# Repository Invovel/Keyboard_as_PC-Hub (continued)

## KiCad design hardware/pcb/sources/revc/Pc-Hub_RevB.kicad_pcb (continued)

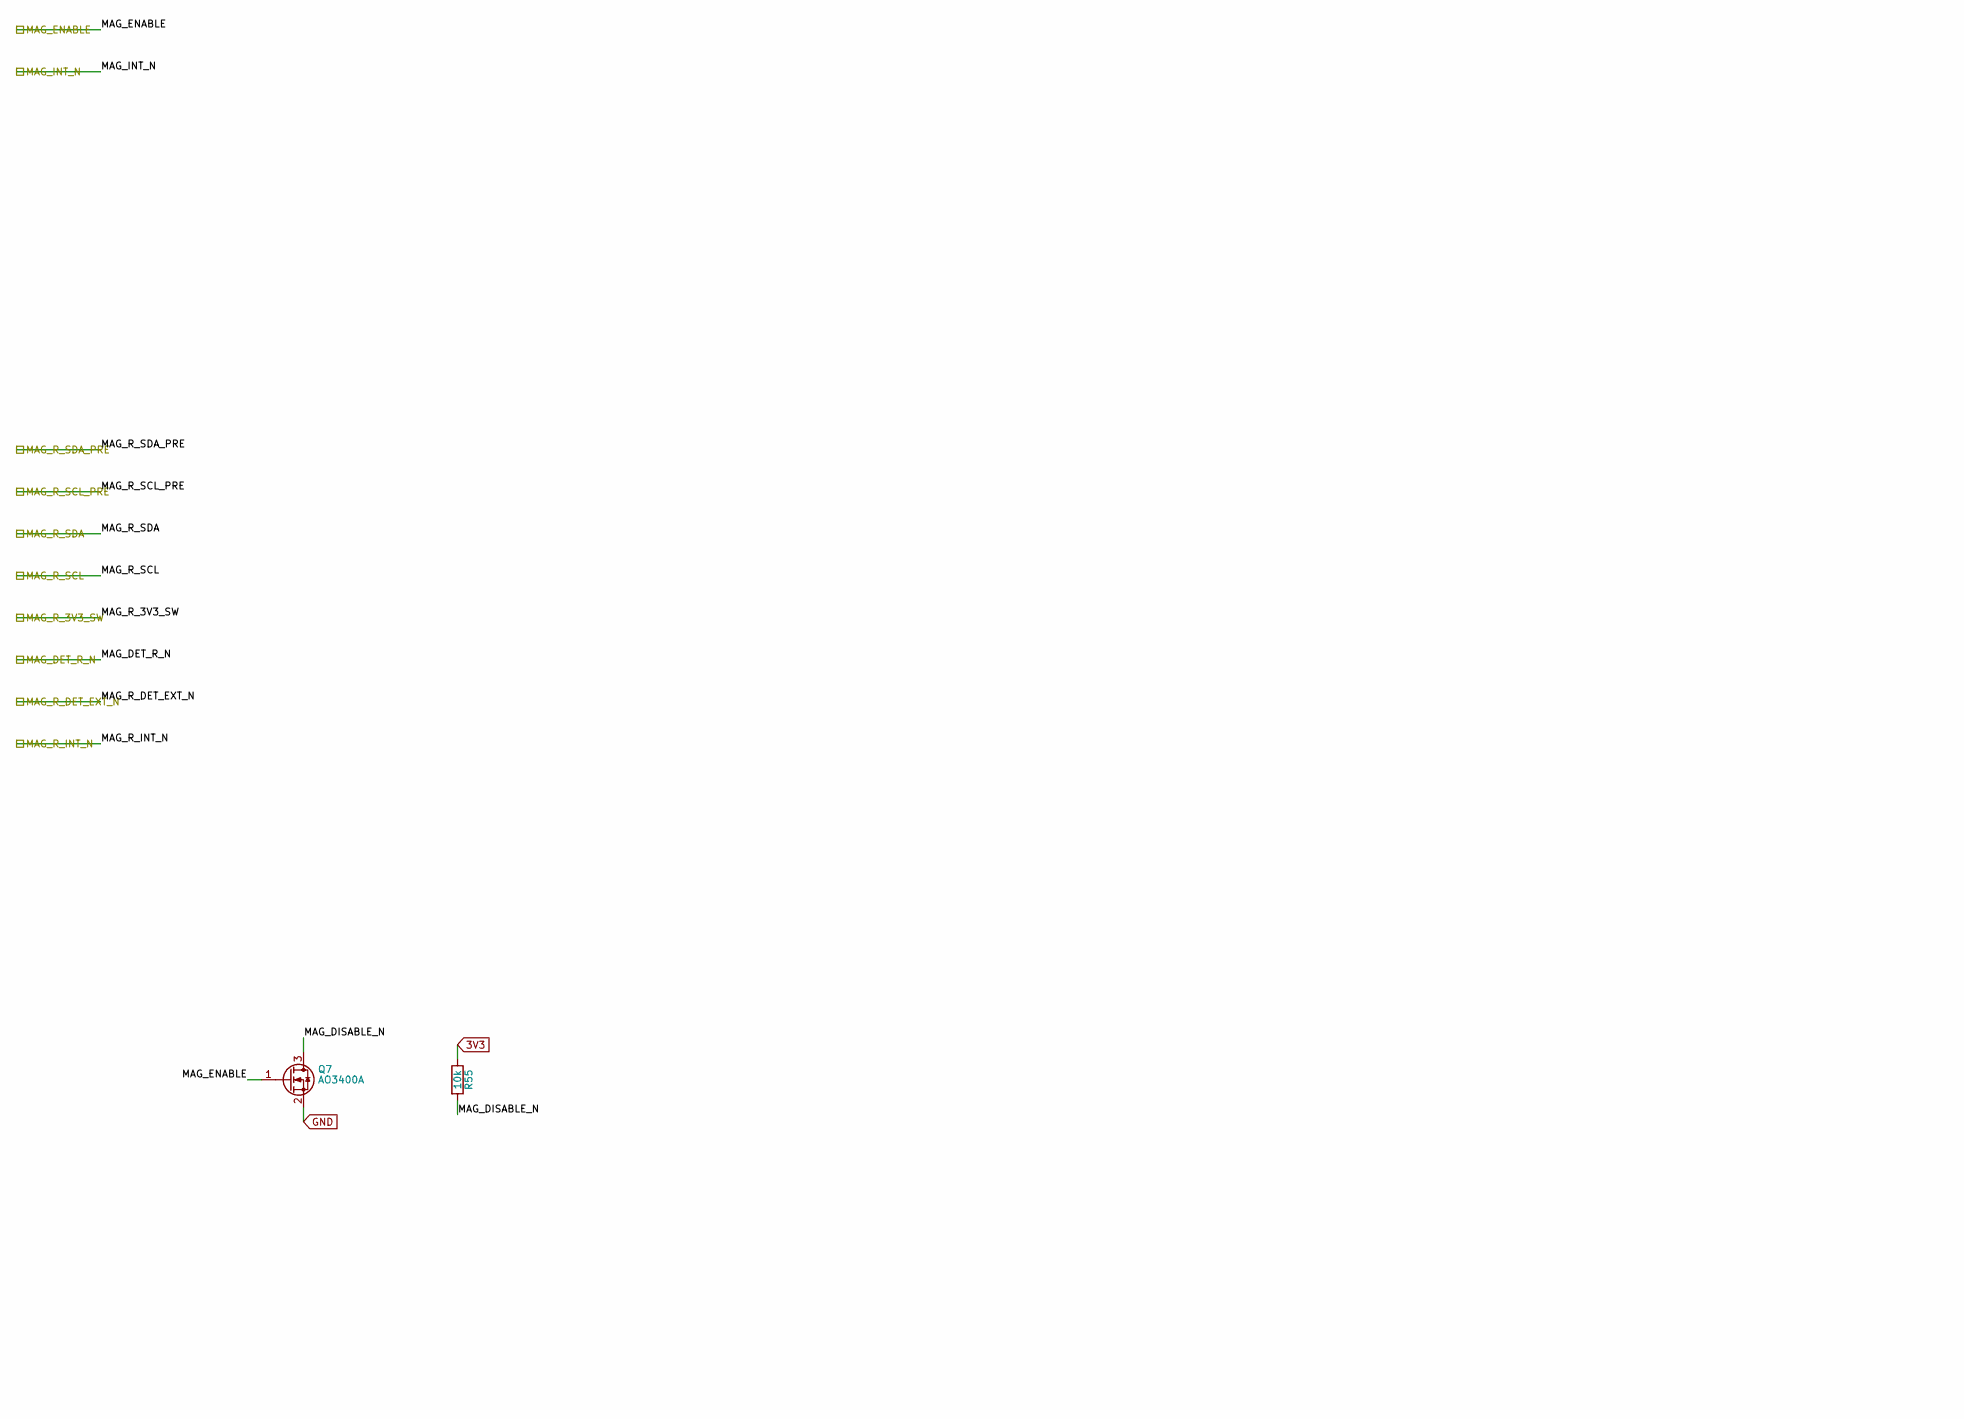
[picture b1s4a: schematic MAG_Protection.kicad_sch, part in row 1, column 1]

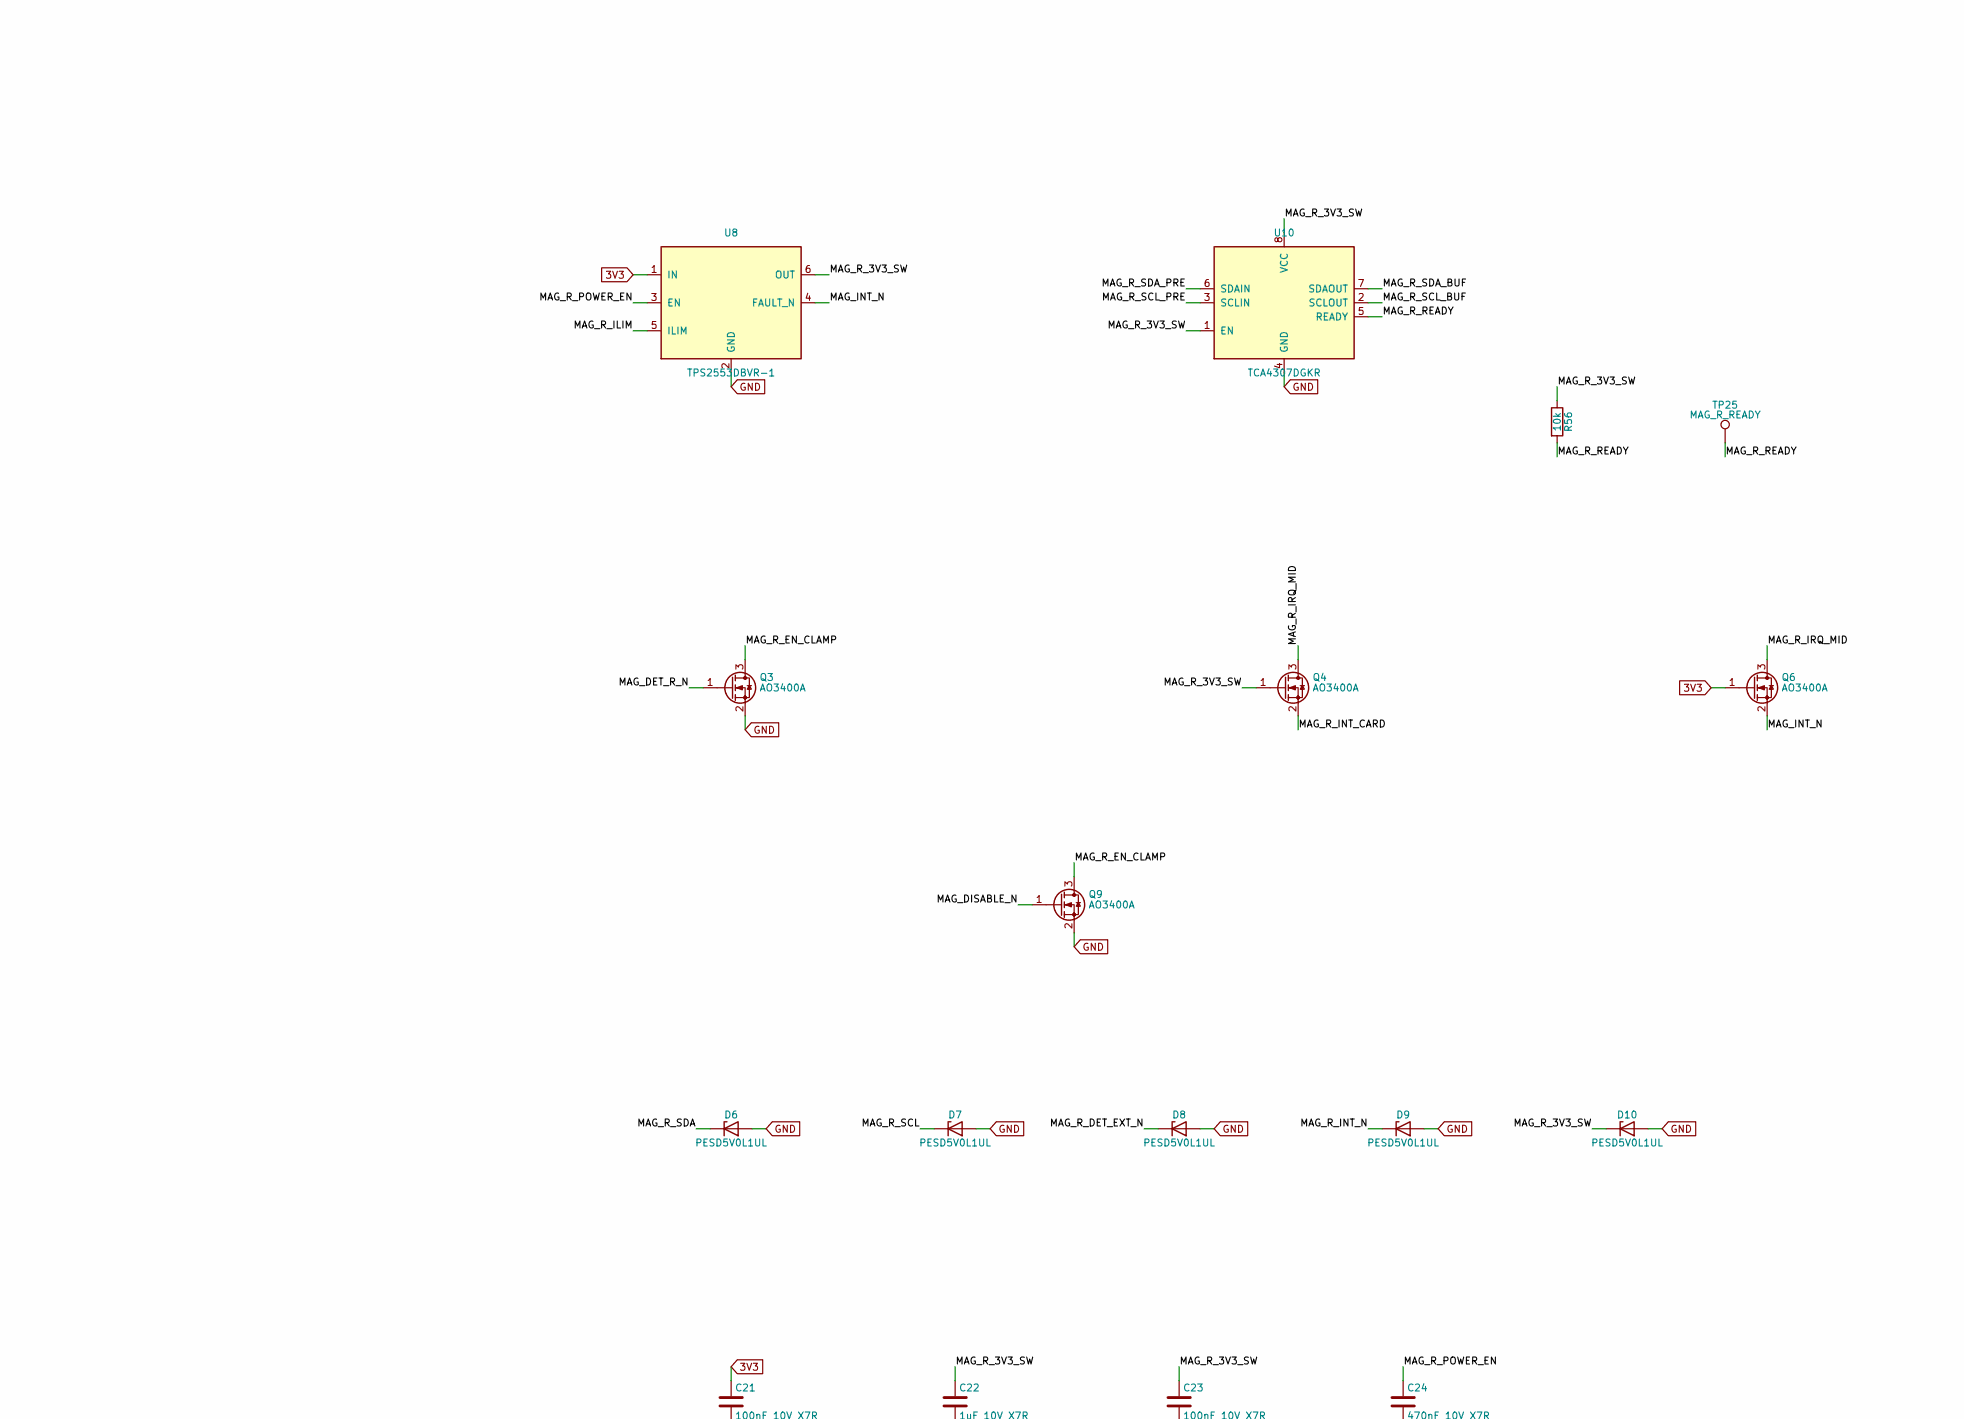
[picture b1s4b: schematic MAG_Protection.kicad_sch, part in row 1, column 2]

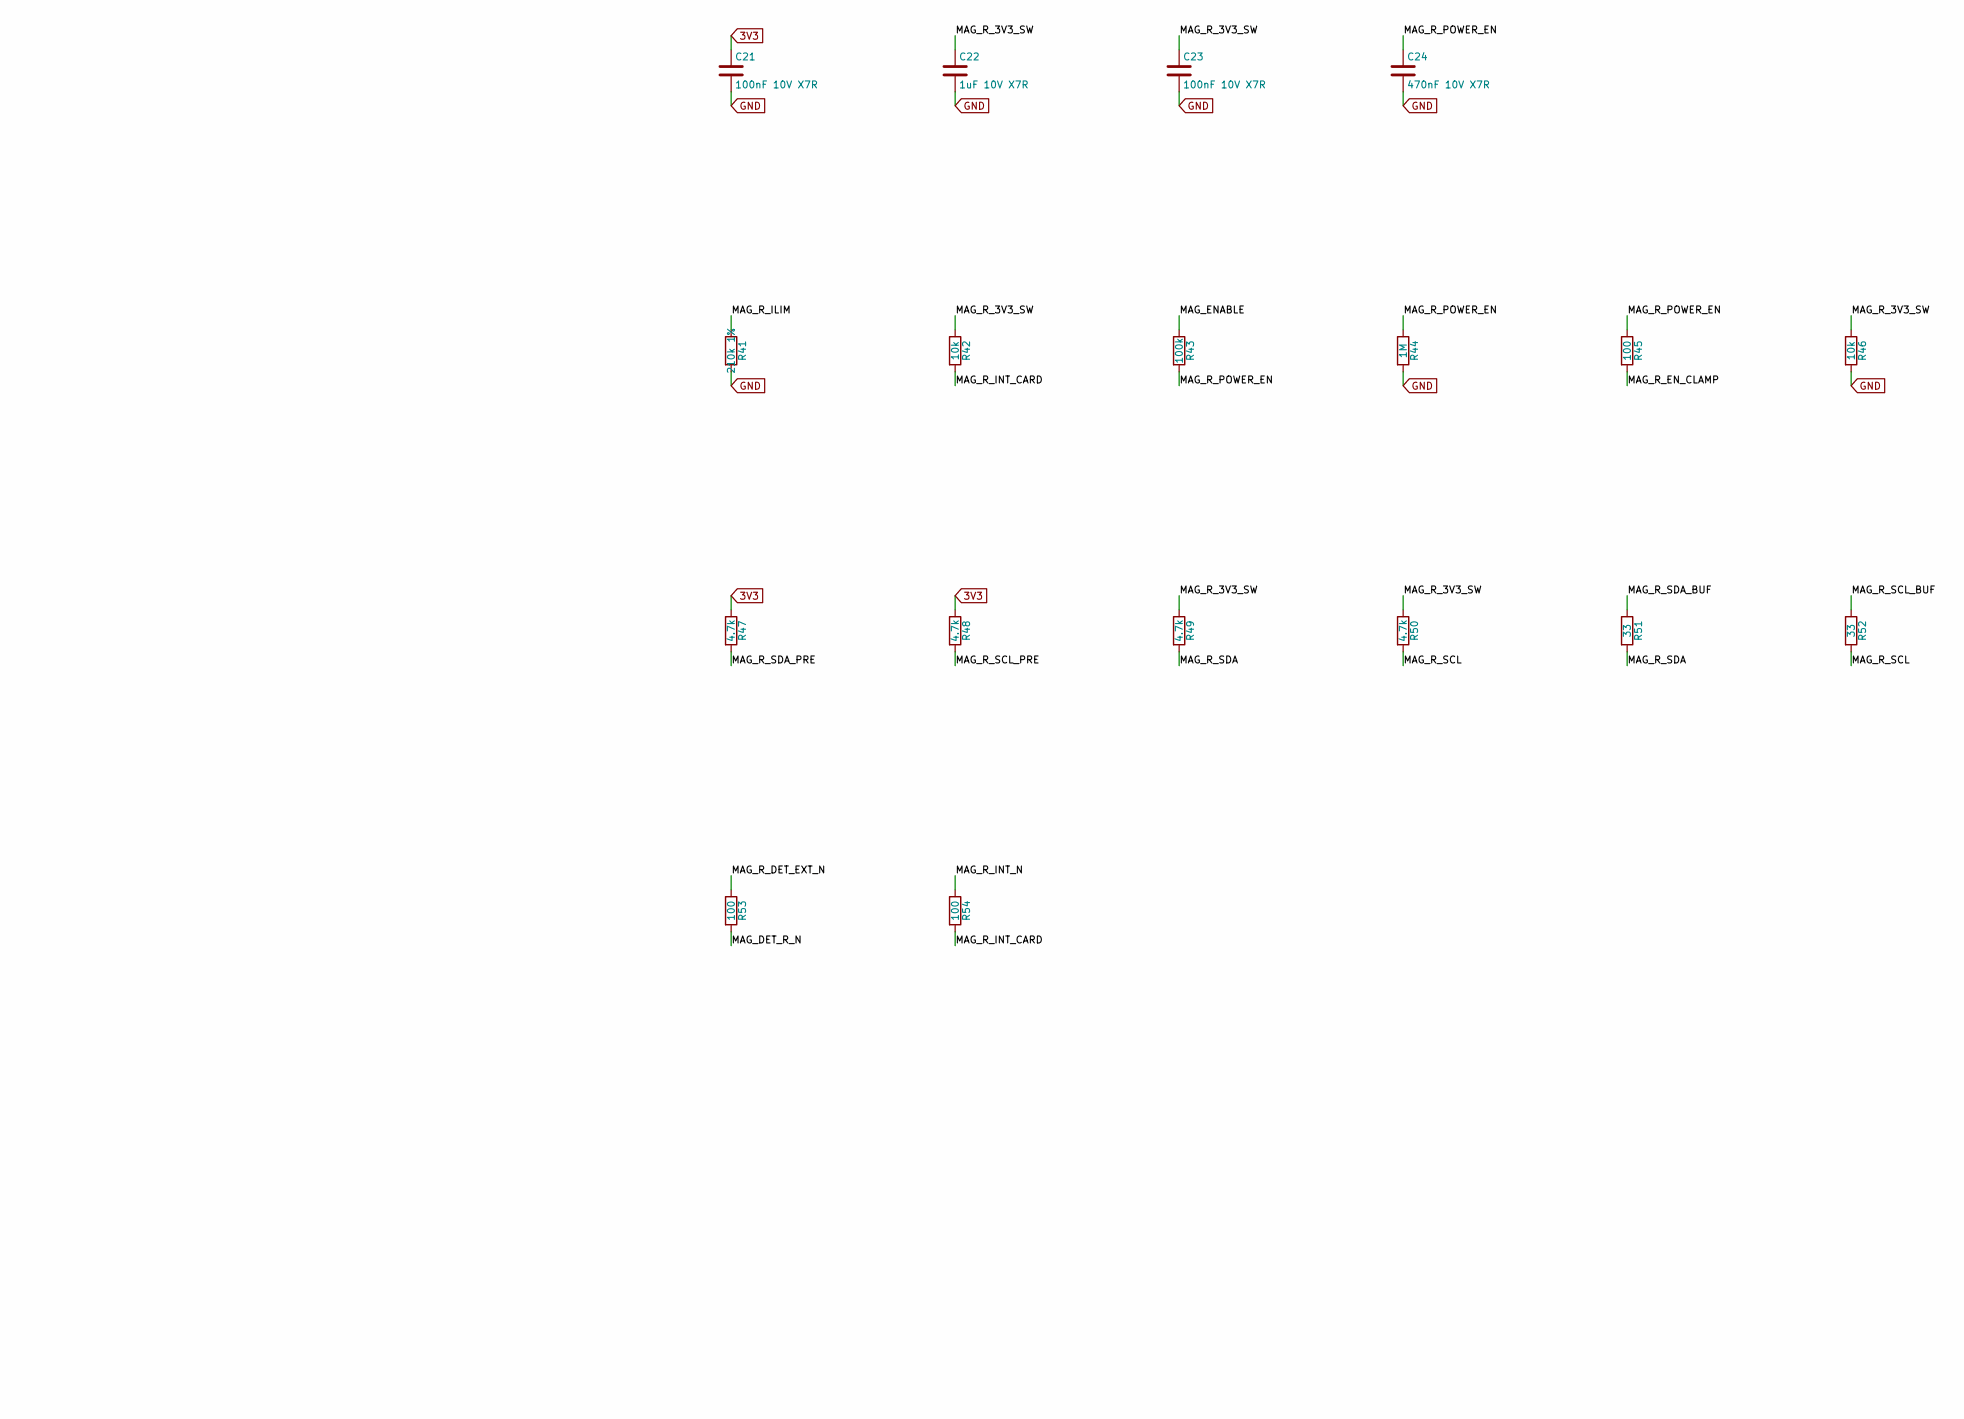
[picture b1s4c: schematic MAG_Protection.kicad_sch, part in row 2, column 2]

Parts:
C21, C23: 100nF 10V X7R; C_0805_2012Metric
C22: 1uF 10V X7R; C_0805_2012Metric
C24: 470nF 10V X7R; C_0805_2012Metric
D6, D7, D8, D9, D10: PESD5V0L1UL; D_SOD-882
Q3, Q4, Q6, Q7, Q9: AO3400A; SOT-23
R41: 210k 1%; R_0603_1608Metric
R42, R46, R55, R56: 10k; R_0603_1608Metric
R43: 100k; R_0603_1608Metric
R44: 1M; R_0603_1608Metric
R45, R53, R54: 100; R_0603_1608Metric
R47, R48, R49, R50: 4.7k; R_0603_1608Metric
R51, R52: 33; R_0603_1608Metric
TP25: MAG_R_READY; TestPoint_Pad_D1.0mm
U8: TPS2553DBVR-1; SOT-23-6
U10: TCA4307DGKR; VSSOP8_TI_DGK0008A

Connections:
3V3: C21.1, Q6.1 (G), R47.1, R48.1, R55.1, U8.1 (IN); also elsewhere on the board
/Main_Control/MAG_DET_R_N: Q3.1 (G), R53.2; also elsewhere on the board
/Main_Control/MAG_ENABLE: Q7.1 (G), R43.1; also elsewhere on the board
/Main_Control/MAG_INT_N: Q6.2 (S), U8.4 (FAULT_N); also elsewhere on the board
/Main_Control/MAG_Protection/MAG_DISABLE_N: Q7.3 (D), Q9.1 (G), R55.2
/Main_Control/MAG_Protection/MAG_R_EN_CLAMP: Q3.3 (D), Q9.3 (D), R45.2
/Main_Control/MAG_Protection/MAG_R_ILIM: R41.1, U8.5 (ILIM)
/Main_Control/MAG_Protection/MAG_R_INT_CARD: Q4.2 (S), R42.2, R54.2
/Main_Control/MAG_Protection/MAG_R_IRQ_MID: Q4.3 (D), Q6.3 (D)
/Main_Control/MAG_Protection/MAG_R_POWER_EN: C24.1, R43.2, R44.1, R45.1, U8.3 (EN)
/Main_Control/MAG_Protection/MAG_R_READY: R56.2, TP25.1, U10.5 (READY)
/Main_Control/MAG_Protection/MAG_R_SCL_BUF: R52.1, U10.2 (SCLOUT)
/Main_Control/MAG_Protection/MAG_R_SDA_BUF: R51.1, U10.7 (SDAOUT)
/Main_Control/MAG_R_3V3_SW: C22.1, C23.1, D10.1 (K), Q4.1 (G), R42.1, R46.1, R49.1, R50.1, R56.1, U8.6 (OUT), U10.1 (EN), U10.8 (VCC); also elsewhere on the board
/Main_Control/MAG_R_DET_EXT_N: D8.1 (K), R53.1; also elsewhere on the board
/Main_Control/MAG_R_INT_N: D9.1 (K), R54.1; also elsewhere on the board
/Main_Control/MAG_R_SCL: D7.1 (K), R50.2, R52.2; also elsewhere on the board
/Main_Control/MAG_R_SCL_PRE: R48.2, U10.3 (SCLIN); also elsewhere on the board
/Main_Control/MAG_R_SDA: D6.1 (K), R49.2, R51.2; also elsewhere on the board
/Main_Control/MAG_R_SDA_PRE: R47.2, U10.6 (SDAIN); also elsewhere on the board
GND: C21.2, C22.2, C23.2, C24.2, D6.2 (A), D7.2 (A), D8.2 (A), D9.2 (A), D10.2 (A), Q3.2 (S), Q7.2 (S), Q9.2 (S), R41.2, R44.2, R46.2, U8.2 (GND), U10.4 (GND); also elsewhere on the board

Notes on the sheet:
RIGHT MAG ONLY: JG2. Current-limit and accessory startup require measurement. U8/Q3/Q7/Q9 retain fault, presence and default-OFF protection. Q4/Q6 isolate IRQ between switched and Core domains. DET is a passive contact to GND; switched pull-ups and TCA4307 retained. Left MAG is retired. SWJ1 uses G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

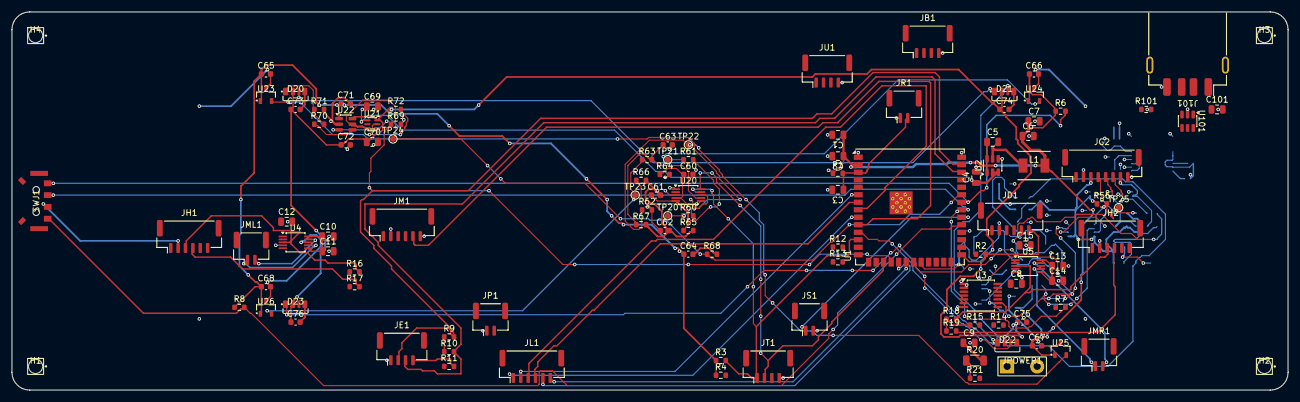
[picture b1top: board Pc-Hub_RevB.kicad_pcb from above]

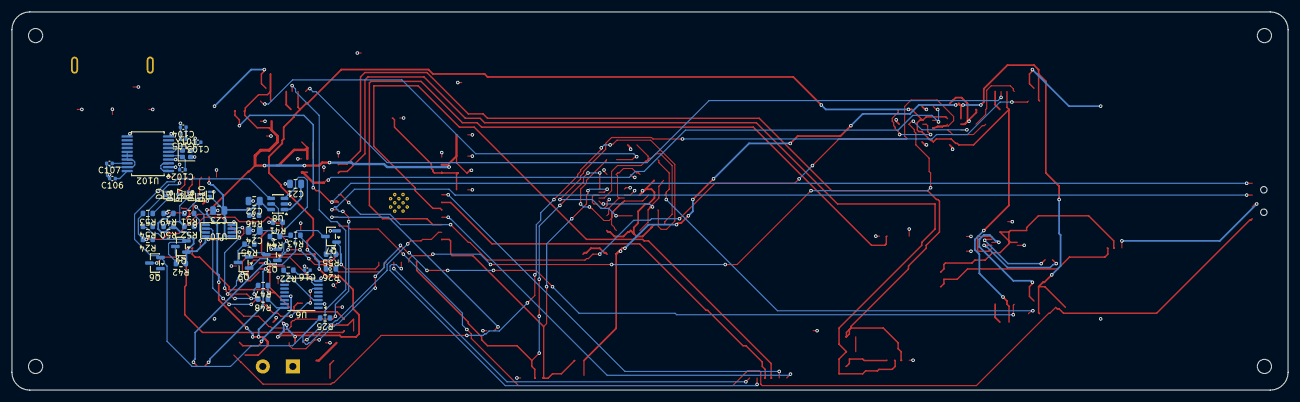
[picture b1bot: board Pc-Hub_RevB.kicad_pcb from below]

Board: 4 copper layers, 216.0 x 64.0 mm, 159 parts (45 on the bottom side), 89 nets.

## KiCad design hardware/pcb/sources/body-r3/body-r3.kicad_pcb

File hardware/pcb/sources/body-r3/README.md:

# R3 模块接口载板草稿

> 本工程保留为历史被动接口载板。本轮没有修改KiCad文件；R3.1原生Core与Dock电气仍待设计，见[最新审查](../../../../docs/R3_1_ENGINEERING_REVIEW.md)。下文100W单体供电及旧生成器说明不代表当前Core结构；不要运行旧生成器覆盖新版参数/图纸，KiCad后续修改须通过Konnect。

这是基于当前已运行固件 GPIO 与模块拓扑生成的 **KiCad 接口原理图 + PCB 布局草稿**。不是 Keychron PCB 的复刻，也不是制造放行板。

按[桌面供电底座定位](../../../../docs/desktop-power-dock.md)，本板是控制载板。新增100W等级PD输入、5V分路供电与USB7206C Hub需要单独子板，**本板J9仍只接5V**；更新产品定位没有实现这些电源电路。

- [body-r3.kicad_pro](body-r3.kicad_pro)：项目入口。
- [body-r3.kicad_sch](body-r3.kicad_sch)：内嵌连接器符号的原理图，11 个逻辑接口。
- [body-r3.kicad_pcb](body-r3.kicad_pcb)：216×64×1.6 mm 板框、34 个网络（包含空网络编号 0）、15 个封装（含安装孔）。**没有走线与铺铜**。
- [generate.py](generate.py)：已停用的旧入口，返回非零且不写文件；[原生成源文本](generate-r3-legacy.py.txt)只供历史阅读。新机械/参数用[update_r3_1.py](../../../enclosure/tools/update_r3_1.py)，后续KiCad变更经Konnect。
- [导出目录](../../exports/body-r3-review/README.md)：接口表、草稿 BOM、布局 SVG、未决事项。

## 可以从现有连接推导什么

屏幕 QSPI、触控 I²C、四键、按压、编码器 A/B、功放 I²S 与新增麦克风 I²S1 的逻辑网络已经明确，因而可以画出模块接口和连接关系。现有 ESP32-S3 开发板的精确型号、针脚排布、安装孔及屏幕背板/FPC 封装未测量，因此 J1/J2 使用**新定义的线束接口**，不假设某块开发板能直接插到这里。

J3/J4 等引脚号也是本载板新定义的线束顺序，不是宣称现有屏幕插座顺序。实际接线必须按模块丝印制作转接线，屏幕排线没有被替换成猜测的 FPC 封装。

## GPIO 基准与歧义处理

当前运行源码和双向日志支持编码器 A=1、B=2、①键=42。用户曾描述把 B 接到 42 后恢复，但当时没有改固件；因此这条口头描述不能直接冻结为 PCB 的 B=42，否则与①键冲突。本草稿以运行源码为基准保留独立网络，实物最终复核前不下单。

## 供电、USB 与磁吸边界

- 本板假设 5V_BODY 和 3V3 来自外部现有模块；没有集成稳压器、反灌保护或 PD。
- J9 是逻辑电源入口，不是 USB-C/PD 端口。现有 USB HID 继续走开发板原生 USB 口；本草稿没有路由 GPIO19/20、高速 USB 或 Hub。
- J10/J11 是左右磁吸转接的焊盘候选。磁吸附件为 DNP，5V_MAG_PROTECTED、3V3_MAG_ISOLATED、MAG_SDA/SCL 等网络未与主体电源/触控总线直连。需要后续限流、热插拔隔离、检测及连接器选型。
- 接点在主板顶面，距外壳端面约 8 mm；需独立 90° 转接小板/柔性连接到端面，不能把平面焊盘当作已完成侧向 pogo 结构。
- 100 nF 及 100 kΩ 等麦克风外围由现成模块承担或后续小板补齐；本次模块载板没有实现裸 INMP441 芯片电路。

## 检查结果

已由 `kiutils 1.4.8` 解析读取 PCB 和原理图，确认网络与接口文件可读；没有安装 KiCad，因此**没有运行 KiCad ERC、DRC，也未确认在 GUI 中打开的效果**。没有 Gerber、贴片坐标或生产就绪声明。

下一步是冻结真实模块封装及主控方案，确定电源/Hub/触点保护，然后布线与 DRC；不能从连接日志自动推断器件机械尺寸或高速电气设计。

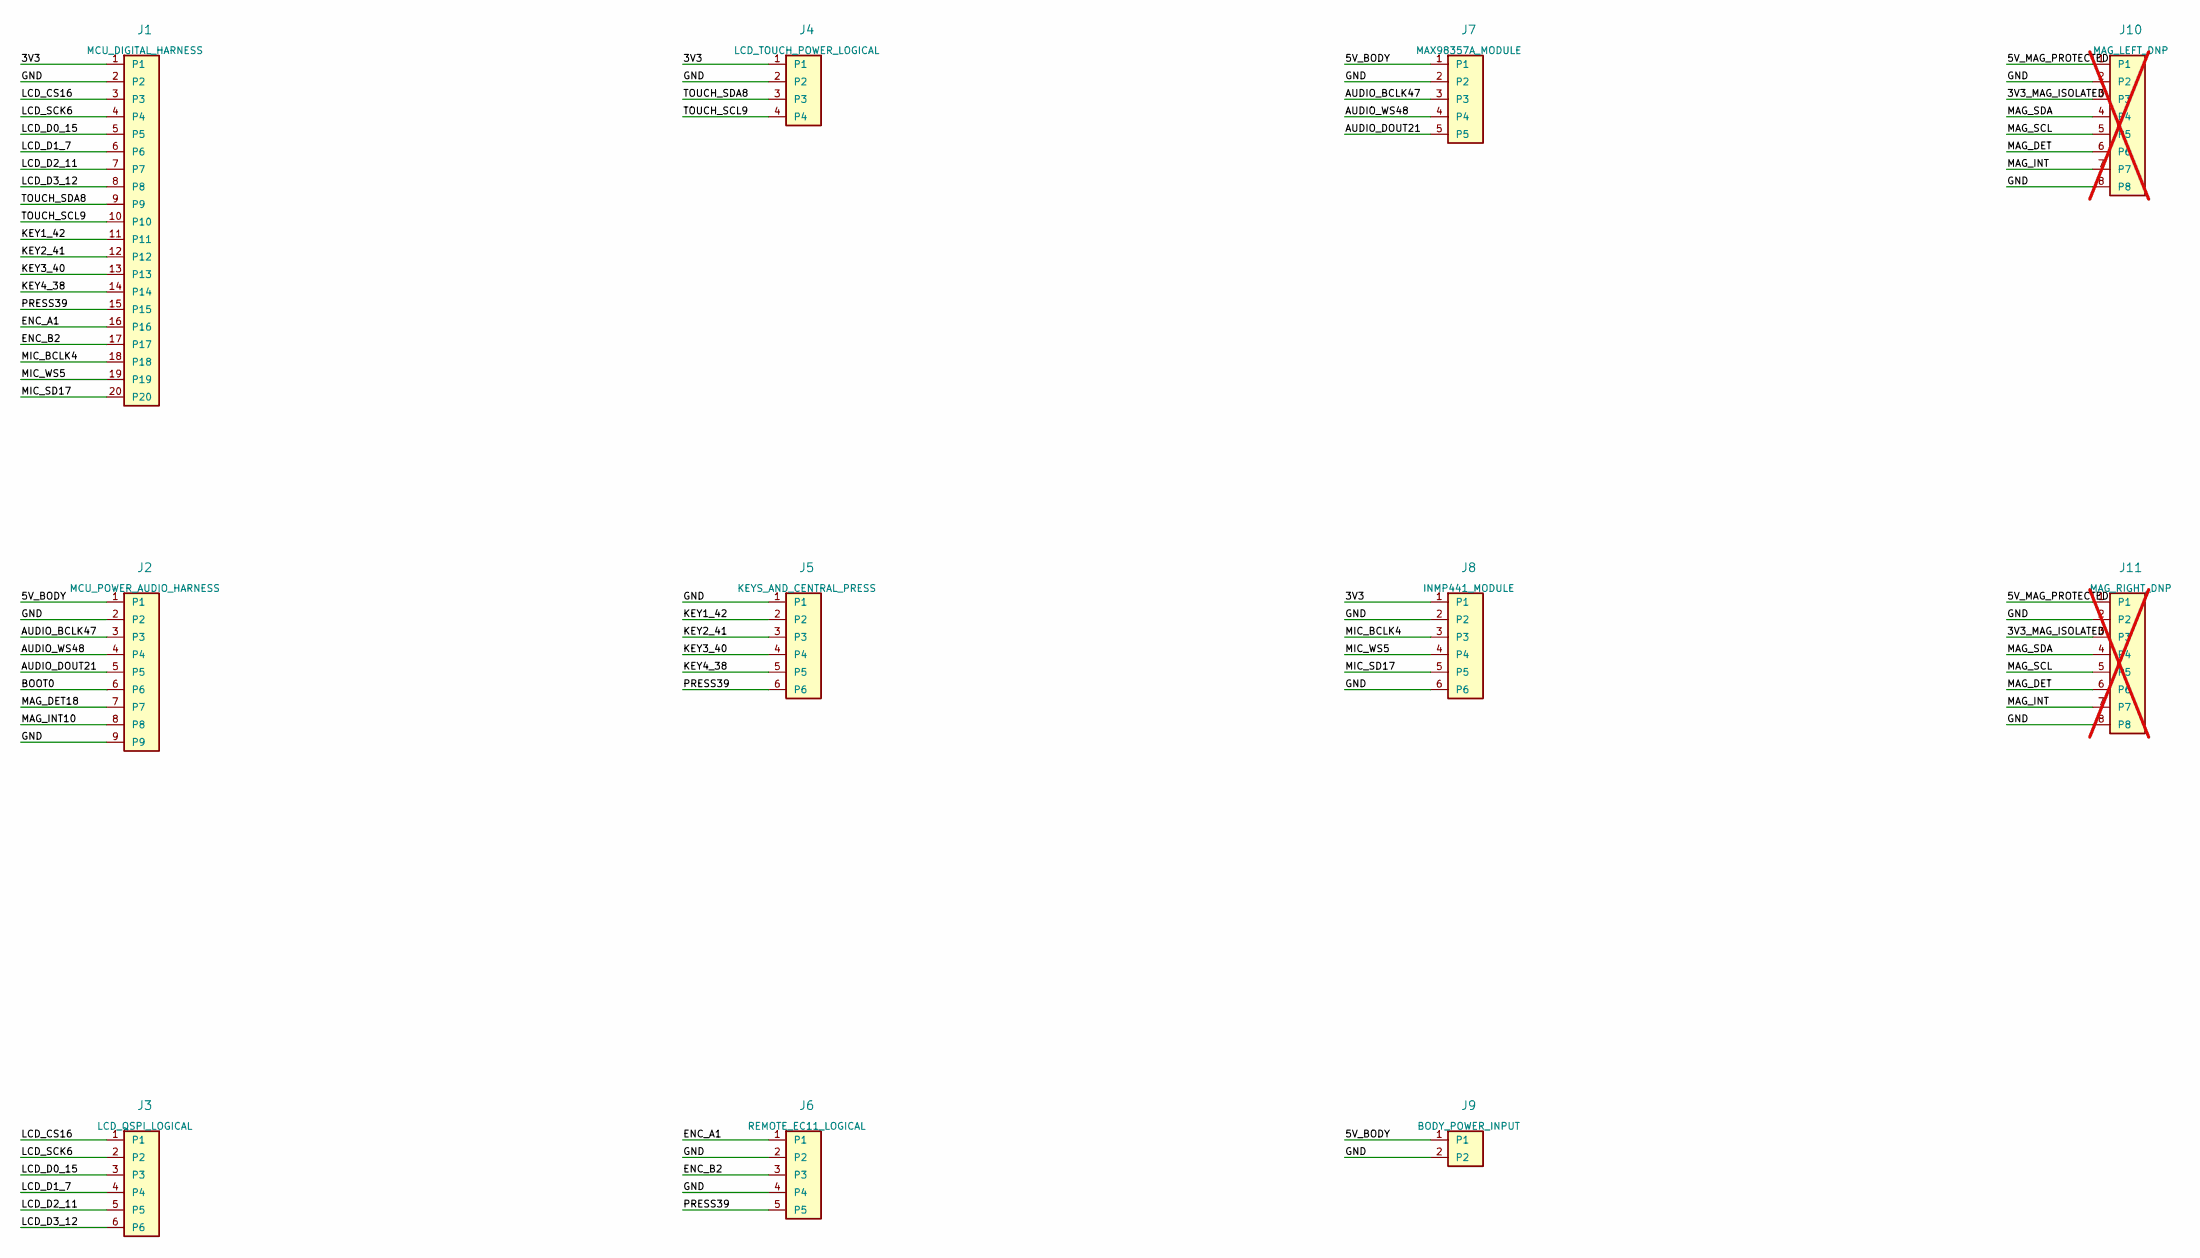
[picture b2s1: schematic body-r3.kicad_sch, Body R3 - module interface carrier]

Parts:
J1: MCU_DIGITAL_HARNESS
J2: MCU_POWER_AUDIO_HARNESS
J3: LCD_QSPI_LOGICAL
J4: LCD_TOUCH_POWER_LOGICAL
J5: KEYS_AND_CENTRAL_PRESS
J6: REMOTE_EC11_LOGICAL
J7: MAX98357A_MODULE
J8: INMP441_MODULE
J9: BODY_POWER_INPUT
J10: MAG_LEFT_DNP; not fitted
J11: MAG_RIGHT_DNP; not fitted

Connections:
3V3: J1.1, J4.1, J8.1
3V3_MAG_ISOLATED: J10.3, J11.3
5V_BODY: J2.1, J7.1, J9.1
5V_MAG_PROTECTED: J10.1, J11.1
AUDIO_BCLK47: J2.3, J7.3
AUDIO_DOUT21: J2.5, J7.5
AUDIO_WS48: J2.4, J7.4
BOOT0: J2.6
ENC_A1: J1.16, J6.1
ENC_B2: J1.17, J6.3
GND: J1.2, J2.2, J2.9, J4.2, J5.1, J6.2, J6.4, J7.2, J8.2, J8.6, J9.2, J10.2, J10.8, J11.2, J11.8
KEY1_42: J1.11, J5.2
KEY2_41: J1.12, J5.3
KEY3_40: J1.13, J5.4
KEY4_38: J1.14, J5.5
LCD_CS16: J1.3, J3.1
LCD_D0_15: J1.5, J3.3
LCD_D1_7: J1.6, J3.4
LCD_D2_11: J1.7, J3.5
LCD_D3_12: J1.8, J3.6
LCD_SCK6: J1.4, J3.2
MAG_DET: J10.6, J11.6
MAG_DET18: J2.7
MAG_INT: J10.7, J11.7
MAG_INT10: J2.8
MAG_SCL: J10.5, J11.5
MAG_SDA: J10.4, J11.4
MIC_BCLK4: J1.18, J8.3
MIC_SD17: J1.20, J8.5
MIC_WS5: J1.19, J8.4
PRESS39: J1.15, J5.6, J6.5
TOUCH_SCL9: J1.10, J4.4
TOUCH_SDA8: J1.9, J4.3

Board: 2 copper layers, 15 parts (0 on the bottom side), 30 nets, no tracks yet.

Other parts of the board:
H1, H2, H3, H4: M2_mount

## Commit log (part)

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2026-03-04 初始提交：STM32键盘Hub工程完整代码框架
